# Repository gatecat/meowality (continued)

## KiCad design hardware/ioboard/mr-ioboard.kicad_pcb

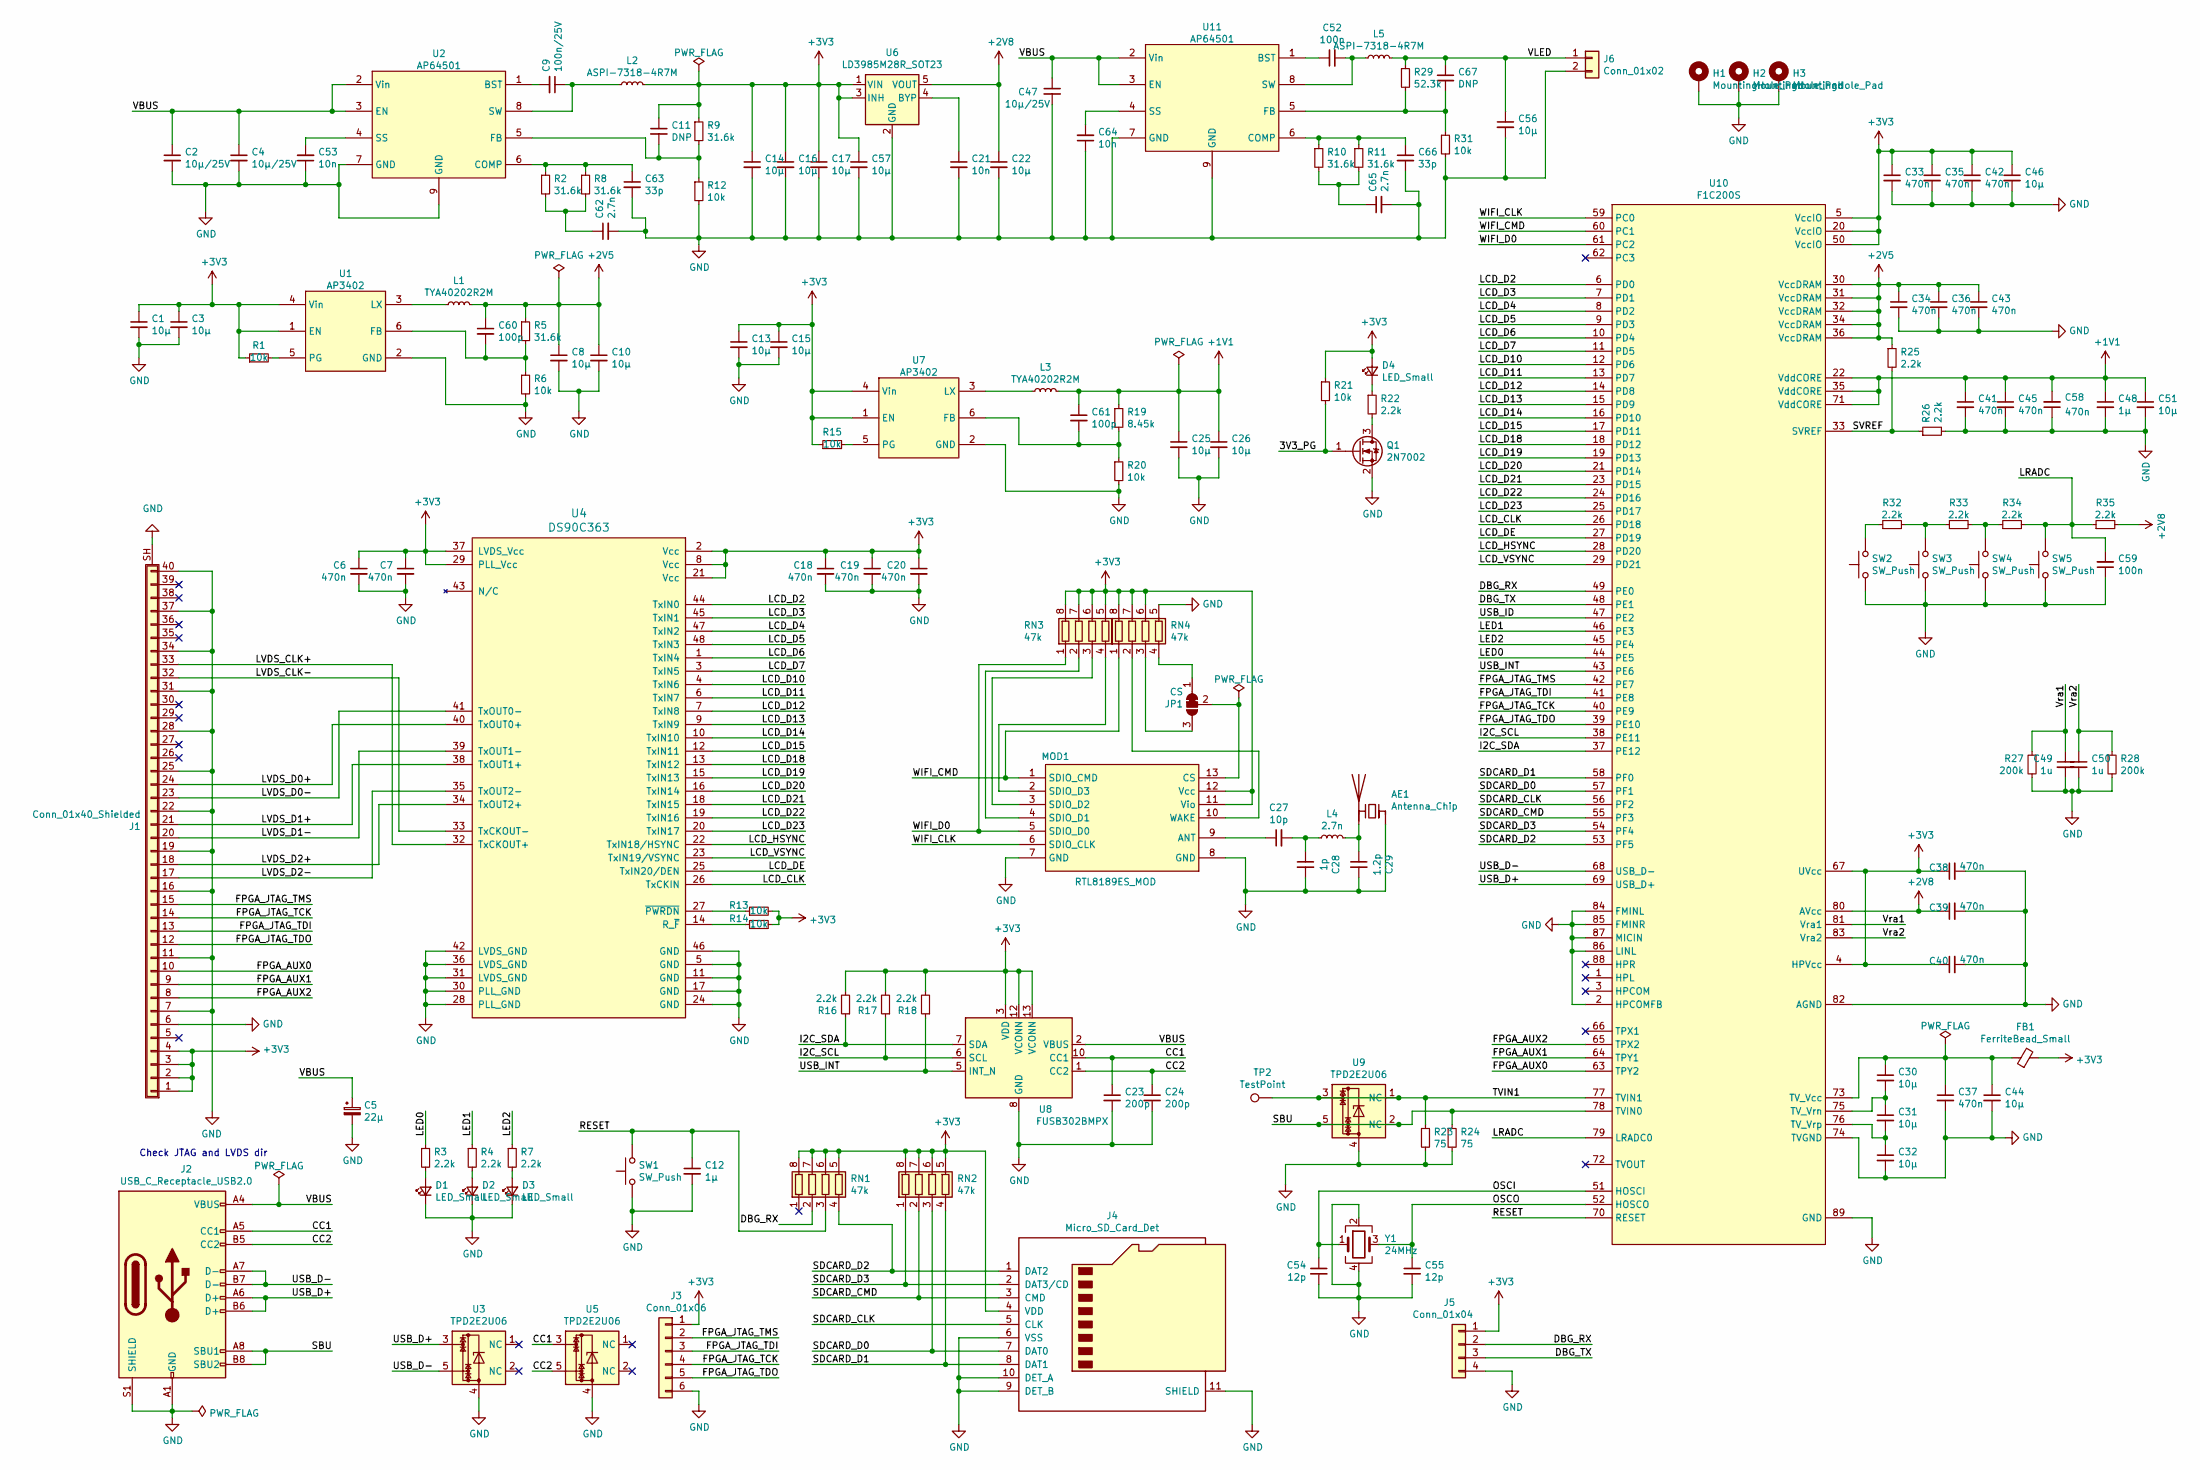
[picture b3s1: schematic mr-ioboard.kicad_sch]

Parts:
AE1: Antenna_Chip; Johanson_2450AT43F0100
C1, C3, C8, C10, C13, C14, C15, C16, C17, C22, C25, C26, C30, C31, C32, C44, C46, C51, C56, C57: 10µ; C_0805_2012Metric
C2, C4, C47: 10µ/25V; C_0805_2012Metric
C5: 22µ; CP_EIA-3528-12_Kemet-T
C6, C7, C18, C19, C20, C33, C34, C35, C36, C37, C38, C39, C40, C41, C42, C43, C45, C58: 470n; C_0402_1005Metric
C9: 100n/25V; C_0402_1005Metric
C11, C67: DNP; C_0402_1005Metric
C12, C48: 1µ; C_0603_1608Metric
C21, C53, C64: 10n; C_0402_1005Metric
C23, C24: 200p; C_0402_1005Metric
C27: 10p; C_0402_1005Metric
C28: 1p; C_0402_1005Metric
C29: 1.2p; C_0402_1005Metric
C49, C50: 1u; C_0603_1608Metric
C52, C59: 100n; C_0402_1005Metric
C54, C55: 12p; C_0402_1005Metric
C60, C61: 100p; C_0402_1005Metric
C62, C65: 2.7n; C_0402_1005Metric
C63, C66: 33p; C_0402_1005Metric
D1, D2, D3, D4: LED_Small; LED_0805_2012Metric
FB1: FerriteBead_Small; L_0603_1608Metric
H1, H2, H3: MountingHole_Pad; MountingHole_3.2mm_M3_Pad_Via
J1: Conn_01x40_Shielded; TE_FPC_40pin_p0.5mm_4-1734839-0
J2: USB_C_Receptacle_USB2.0; USB_C_Receptacle_GCT_USB4085
J3: Conn_01x06; PinHeader_1x06_P2.54mm_Vertical
J4: Micro_SD_Card_Det; microSD_HC_Hirose_DM3BT-DSF-PEJS
J5: Conn_01x04; PinHeader_1x04_P2.54mm_Vertical
J6: Conn_01x02; PinHeader_1x02_P2.54mm_Vertical
JP1: CS; SolderJumper-3_P1.3mm_Bridged12_Pad1.0x1.5mm
L1, L3: TYA40202R2M; L_Taiyo-Yuden_NR-40xx
L2, L5: ASPI-7318-4R7M; L_Bourns_SRP7028A_7.3x6.6mm
L4: 2.7n; L_0402_1005Metric
MOD1: RTL8189ES_MOD
Q1: 2N7002; SOT-23
R1, R6, R12, R13, R14, R15, R20, R21, R31: 10k; R_0402_1005Metric
R2, R5, R8, R9, R10, R11: 31.6k; R_0402_1005Metric
R3, R4, R7, R16, R17, R18, R22, R25, R26, R32, R33, R34, R35: 2.2k; R_0402_1005Metric
R19: 8.45k; R_0402_1005Metric
R23, R24: 75; R_0402_1005Metric
R27, R28: 200k; R_0402_1005Metric
R29: 52.3k; R_0402_1005Metric
RN1, RN2, RN3, RN4: 47k; R_Array_Convex_4x0402
SW1, SW2, SW3, SW4, SW5: SW_Push; SW_SPST_B3U-3000P
TP2: TestPoint; TestPoint_Pad_D2.0mm
U1, U7: AP3402; TSOT-23-6
U2, U11: AP64501; Diodes_SO-8EP
U3, U5, U9: TPD2E2U06; SOT-553
U4: DS90C363; TSSOP-48_8x12.5mm_P0.5mm
U6: LD3985M28R_SOT23; SOT-23-5
U8: FUSB302BMPX; WQFN-14-1EP_2.5x2.5mm_P0.5mm_EP1.45x1.45mm
U10: F1C200S; QFN-88_EP_10x10_Pitch0.4mm
Y1: 24MHz; Oscillator_SMD_EuroQuartz_XO32-4Pin_3.2x2.5mm

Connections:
+1V1: C25.1, C26.1, C41.1, C45.1, C48.1, C51.1, C58.2, C61.1, L3.2, R19.1, U10.22 (VddCORE), U10.35 (VddCORE), U10.71 (VddCORE)
+2V5: C8.1, C10.1, C34.1, C36.1, C43.1, C60.1, L1.2, R5.1, R25.1, U10.30 (VccDRAM), U10.31 (VccDRAM), U10.32 (VccDRAM), U10.34 (VccDRAM), U10.36 (VccDRAM)
+2V8: C22.1, C39.1, R35.2, U6.5 (VOUT), U10.80 (AVcc)
+3V3: C1.1, C3.1, C6.1, C7.1, C11.1, C13.1, C14.1, C15.1, C16.1, C17.1, C18.1, C19.1, C20.1, C33.1, C35.1, C38.1, C40.1, C42.1, C46.1, C57.1, D4.2 (A), FB1.2, J1.1, J1.2, J1.3, J1.4, J3.1, J4.4 (VDD), J5.1, L2.2, MOD1.11 (Vio), MOD1.12 (Vcc), R1.1, R9.1, R13.2, R14.2, R15.1, R16.2, R17.2, R18.2, R21.1, RN1.5 (R4.2), RN1.6 (R3.2), RN1.7 (R2.2), RN1.8 (R1.2), RN2.5 (R4.2), RN2.6 (R3.2), RN2.7 (R2.2), RN2.8 (R1.2), RN3.5 (R4.2), RN3.6 (R3.2), RN3.7 (R2.2), RN3.8 (R1.2), RN4.6 (R3.2), RN4.7 (R2.2), RN4.8 (R1.2), U1.1 (EN), U1.4 (Vin), U4.2 (Vcc), U4.8 (Vcc), U4.21 (Vcc), U4.29 (PLL_Vcc), U4.37 (LVDS_Vcc), U6.1 (VIN), U6.3 (INH), U7.1 (EN), U7.4 (Vin), U8.3 (VDD), U8.4 (VDD), U8.12 (VCONN), U8.13 (VCONN), U10.4 (HPVcc), U10.5 (VccIO), U10.20 (VccIO), U10.50 (VccIO), U10.67 (UVcc)
/3V3_PG: Q1.1 (G), R21.2
/CC1: C23.1, J2.A5 (CC1), U5.3, U8.10 (CC1), U8.11 (CC1)
/CC2: C24.1, J2.B5 (CC2), U5.5, U8.1 (CC2), U8.14 (CC2)
/DBG_RX: J5.2, RN1.2 (R2.1), U10.49 (PE0)
/DBG_TX: J5.3, U10.48 (PE1)
/FPGA_AUX0: J1.10, U10.63 (TPY2)
/FPGA_AUX1: J1.9, U10.64 (TPY1)
/FPGA_AUX2: J1.8, U10.65 (TPX2)
/FPGA_JTAG_TCK: J1.14, J3.4, U10.40 (PE9)
/FPGA_JTAG_TDI: J1.13, J3.3, U10.41 (PE8)
/FPGA_JTAG_TDO: J1.12, J3.5, U10.39 (PE10)
/FPGA_JTAG_TMS: J1.15, J3.2, U10.42 (PE7)
/I2C_SCL: R17.1, U8.6 (SCL), U10.38 (PE11)
/I2C_SDA: R16.1, U8.7 (SDA), U10.37 (PE12)
/LCD_CLK: U4.26 (TxCKIN), U10.26 (PD18)
/LCD_D2: U4.44 (TxIN0), U10.6 (PD0)
/LCD_D3: U4.45 (TxIN1), U10.7 (PD1)
/LCD_D4: U4.47 (TxIN2), U10.8 (PD2)
/LCD_D5: U4.48 (TxIN3), U10.9 (PD3)
/LCD_D6: U4.1 (TxIN4), U10.10 (PD4)
/LCD_D7: U4.3 (TxIN5), U10.11 (PD5)
/LCD_D10: U4.4 (TxIN6), U10.12 (PD6)
/LCD_D11: U4.6 (TxIN7), U10.13 (PD7)
/LCD_D12: U4.7 (TxIN8), U10.14 (PD8)
/LCD_D13: U4.9 (TxIN9), U10.15 (PD9)
/LCD_D14: U4.10 (TxIN10), U10.16 (PD10)
/LCD_D15: U4.12 (TxIN11), U10.17 (PD11)
/LCD_D18: U4.13 (TxIN12), U10.18 (PD12)
/LCD_D19: U4.15 (TxIN13), U10.19 (PD13)
/LCD_D20: U4.16 (TxIN14), U10.21 (PD14)
/LCD_D21: U4.18 (TxIN15), U10.23 (PD15)
/LCD_D22: U4.19 (TxIN16), U10.24 (PD16)
/LCD_D23: U4.20 (TxIN17), U10.25 (PD17)
/LCD_DE: U4.25 (TxIN20/DEN), U10.27 (PD19)
/LCD_HSYNC: U4.22 (TxIN18/HSYNC), U10.28 (PD20)
/LCD_VSYNC: U4.23 (TxIN19/VSYNC), U10.29 (PD21)
/LED0: R3.1, U10.44 (PE5)
/LED1: R4.1, U10.46 (PE3)
/LED2: R7.1, U10.45 (PE4)
/LRADC: C59.2, R34.2, R35.1, SW5.2, U10.79 (LRADC0)
/LVDS_CLK+: J1.33, U4.32 (TxCKOUT+)
/LVDS_CLK-: J1.32, U4.33 (TxCKOUT-)
/LVDS_D0+: J1.24, U4.40 (TxOUT0+)
/LVDS_D0-: J1.23, U4.41 (TxOUT0-)
/LVDS_D1+: J1.21, U4.38 (TxOUT1+)
/LVDS_D1-: J1.20, U4.39 (TxOUT1-)
/LVDS_D2+: J1.18, U4.34 (TxOUT2+)
/LVDS_D2-: J1.17, U4.35 (TxOUT2-)
/OSCI: C54.1, U10.51 (HOSCI), Y1.1
/OSCO: C55.1, U10.52 (HOSCO), Y1.3
/RESET: C12.1, RN1.3 (R3.1), SW1.2, U10.70 (RESET)
/SBU: J2.A8 (SBU1), J2.B8 (SBU2), R24.1, U9.2 (NC), U9.5, U10.78 (TVIN0)
/SDCARD_CLK: J4.5 (CLK), U10.56 (PF2)
/SDCARD_CMD: J4.3 (CMD), RN2.2 (R2.1), U10.55 (PF3)
/SDCARD_D0: J4.7 (DAT0), RN2.3 (R3.1), U10.57 (PF1)
/SDCARD_D1: J4.8 (DAT1), RN2.4 (R4.1), U10.58 (PF0)
/SDCARD_D2: J4.1 (DAT2), RN1.4 (R4.1), U10.53 (PF5)
/SDCARD_D3: J4.2 (DAT3/CD), RN2.1 (R1.1), U10.54 (PF4)
/SVREF: R25.2, R26.1, U10.33 (SVREF)
/TVIN1: R23.1, TP2.1, U9.1 (NC), U9.3, U10.77 (TVIN1)
/USB_D+: J2.A6 (D+), J2.B6 (D+), U3.3, U10.69 (USB_D+)
/USB_D-: J2.A7 (D-), J2.B7 (D-), U3.5, U10.68 (USB_D-)
/USB_ID: U10.47 (PE2)
/USB_INT: R18.1, U8.5 (INT_N), U10.43 (PE6)
/VBUS: C2.1, C4.1, C5.1, C47.1, J2.A4 (VBUS), J2.A9 (VBUS), J2.B4 (VBUS), J2.B9 (VBUS), U2.2 (Vin), U2.3 (EN), U8.2 (VBUS), U11.2 (Vin), U11.3 (EN)
/VLED: C56.1, C67.1, J6.1, L5.2, R29.1
/Vra1: C49.1, R27.1, U10.81 (Vra1)
/Vra2: C50.1, R28.1, U10.83 (Vra2)
/WIFI_CLK: MOD1.6 (SDIO_CLK), U10.59 (PC0)
/WIFI_CMD: MOD1.1 (SDIO_CMD), RN4.1 (R1.1), U10.60 (PC1)
/WIFI_D0: MOD1.5 (SDIO_D0), RN3.1 (R1.1), U10.61 (PC2)
GND: AE1.1 (FEED), C1.2, C2.2, C3.2, C4.2, C5.2, C6.2, C7.2, C8.2, C10.2, C12.2, C13.2, C14.2, C15.2, C16.2, C17.2, C18.2, C19.2, C20.2, C21.2, C22.2, C23.2, C24.2, C25.2, C26.2, C28.2, C29.2, C32.2, C33.2, C34.2, C35.2, C36.2, C37.2, C38.2, C39.2, C40.2, C41.2, C42.2, C43.2, C44.2, C45.2, C46.2, C47.2, C48.2, C49.2, C50.2, C51.2, C53.1, C54.2, C55.2, C56.2, C57.2, C58.1, C59.1, C62.2, C63.2, C64.1, C65.2, C66.2, D1.1 (K), D2.1 (K), D3.1 (K), H1.1, H2.1, H3.1, J1.6, J1.7, J1.11, J1.16, J1.19, J1.22, J1.25, J1.28, J1.31, J1.34, J1.37, J1.40, J1.SH (Shield), J2.A1 (GND), J2.A12 (GND), J2.B1 (GND), J2.B12 (GND), J2.S1 (SHIELD), J3.6, J4.6 (VSS), J4.9 (DET_B), J4.10 (DET_A), J4.11 (SHIELD), J5.4, J6.2, MOD1.7 (GND), MOD1.8 (GND), Q1.2 (S), R6.2, R12.2, R20.2, R23.2, R24.2, R26.2, R27.2, R28.2, R31.2, RN4.5 (R4.2), SW1.1, SW2.1, SW3.1, SW4.1, SW5.1, U1.2 (GND), U2.7 (GND), U2.9 (GND), U3.4, U4.5 (GND), U4.11 (GND), U4.17 (GND), U4.24 (GND), U4.28 (PLL_GND), U4.30 (PLL_GND), U4.31 (LVDS_GND), U4.36 (LVDS_GND), U4.42 (LVDS_GND), U4.46 (GND), U5.4, U6.2 (GND), U7.2 (GND), U8.8 (GND), U8.9 (GND), U8.15 (GND), U9.4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
unnamed: AE1.2 (PCB_Trace), C29.1, L4.2
unnamed: C9.1, L2.1, U2.8 (SW)
unnamed: C9.2, U2.1 (BST)
unnamed: C11.2, R9.2, R12.1, U2.5 (FB)
unnamed: C21.1, U6.4 (BYP)
unnamed: C27.1, MOD1.9 (ANT)
unnamed: C27.2, C28.1, L4.1
unnamed: C30.1, C37.1, C44.1, FB1.1, U10.73 (TV_Vcc)
unnamed: C30.2, C31.1, U10.75 (TV_Vrn)
unnamed: C31.2, C32.1, U10.76 (TV_Vrp)
unnamed: C52.1, U11.1 (BST)
unnamed: C52.2, L5.1, U11.8 (SW)
unnamed: C53.2, U2.4 (SS)
unnamed: C60.2, R5.2, R6.1, U1.6 (FB)
unnamed: C61.2, R19.2, R20.1, U7.6 (FB)
unnamed: C62.1, R2.2, R8.2
unnamed: C63.1, R2.1, R8.1, U2.6 (COMP)
unnamed: C64.2, U11.4 (SS)
unnamed: C65.1, R10.2, R11.2
unnamed: C66.1, R10.1, R11.1, U11.6 (COMP)
unnamed: C67.2, R29.2, R31.1, U11.5 (FB)
unnamed: D1.2 (A), R3.2
unnamed: D2.2 (A), R4.2
unnamed: D3.2 (A), R7.2
unnamed: D4.1 (K), R22.1
unnamed: JP1.1 (A), RN4.4 (R4.1)
unnamed: JP1.2 (C), MOD1.13 (CS)
unnamed: JP1.3 (B), RN4.3 (R3.1)
unnamed: L1.1, U1.3 (LX)
unnamed: L3.1, U7.3 (LX)
unnamed: MOD1.2 (SDIO_D3), RN3.4 (R4.1)
unnamed: MOD1.3 (SDIO_D2), RN3.3 (R3.1)
unnamed: MOD1.4 (SDIO_D1), RN3.2 (R2.1)
unnamed: MOD1.10 (WAKE), RN4.2 (R2.1)
unnamed: Q1.3 (D), R22.2
unnamed: R1.2, U1.5 (PG)
unnamed: R13.1, U4.27 (~PWRDN)
unnamed: R14.1, U4.14 (R_~F)
unnamed: R15.2, U7.5 (PG)
unnamed: R32.1, SW2.2
unnamed: R32.2, R33.1, SW3.2
unnamed: R33.2, R34.1, SW4.2

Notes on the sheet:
Check JTAG and LVDS dir

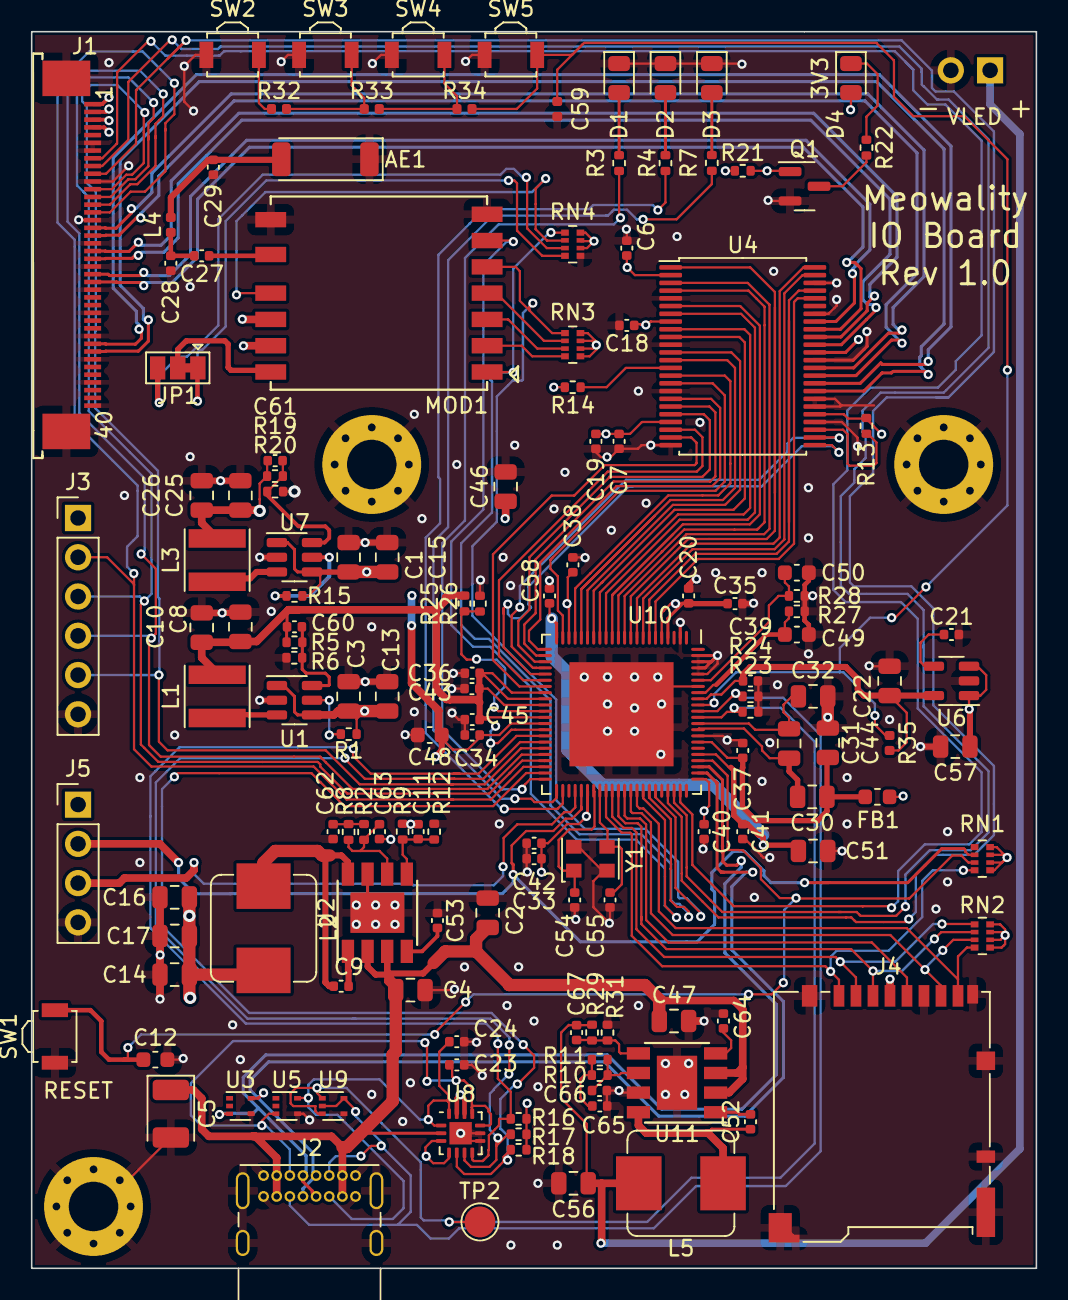
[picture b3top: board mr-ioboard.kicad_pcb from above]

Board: 4 copper layers, 65.0 x 80.0 mm, 146 parts (1 on the bottom side), 117 nets.

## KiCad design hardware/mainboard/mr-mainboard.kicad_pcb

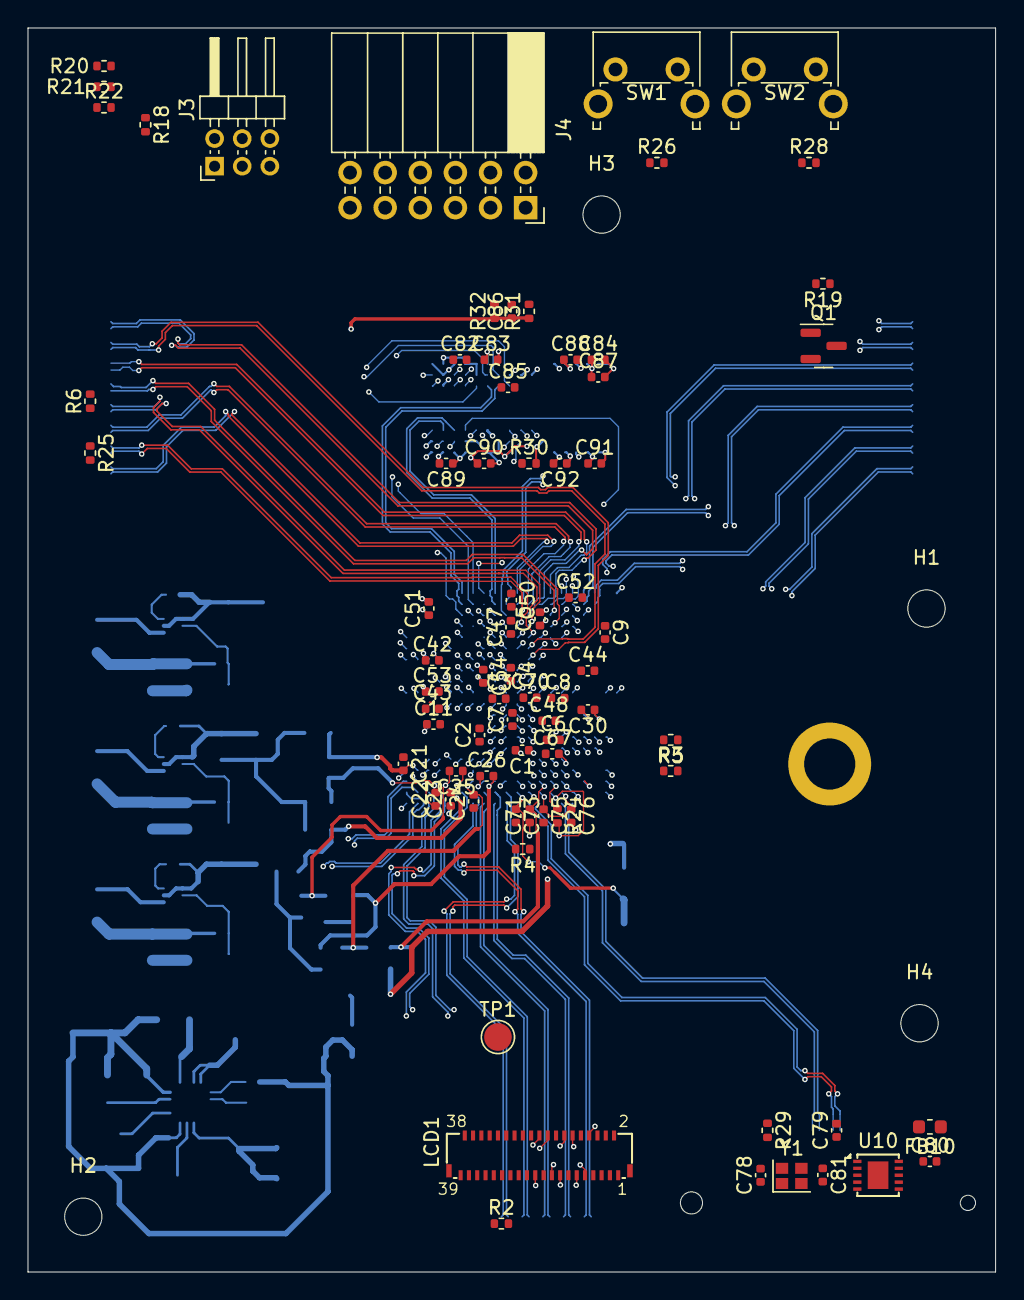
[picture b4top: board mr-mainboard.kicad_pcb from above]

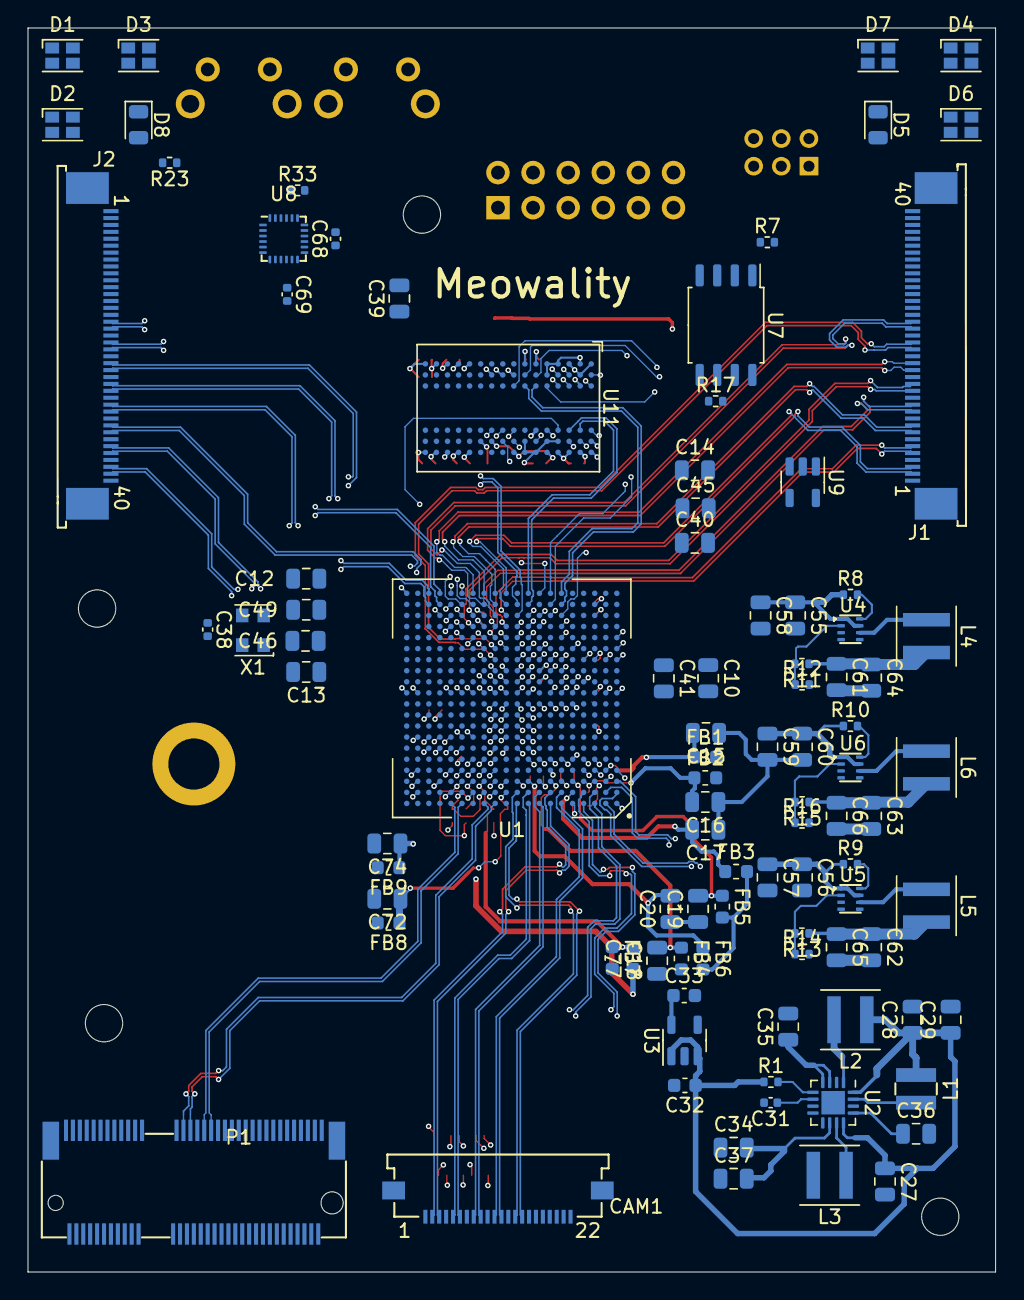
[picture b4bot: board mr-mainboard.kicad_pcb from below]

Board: 6 copper layers, 70.0 x 90.0 mm, 177 parts (96 on the bottom side), 193 nets.

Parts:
C1, C2, C3, C4, C5, C6, C7, C8, C9, C11, C38, C42, C43, C44, C47, C48, C50, C51, C52, C53, C54, C67, C68, C70, C79, C80, C82, C83, C84, C85, C86, C87, C88, C89, C90, C91, C92: 470n; C_0402_1005Metric
C10, C12, C13, C14, C15, C16, C17, C18, C19, C20, C27, C28, C29, C34, C35, C36, C37, C39, C40, C41, C45, C46, C49, C55, C56, C57, C58, C59, C60, C61, C62, C63, C64, C65, C66, C72, C74: 10µ; C_0805_2012Metric
C21, C22, C23, C24, C25, C26, C30, C31, C69, C71, C73, C75, C76: 100n; C_0402_1005Metric
C32, C33: 1µ; C_0603_1608Metric
C77: 2.2µ; C_0603_1608Metric
C78, C81: 12p; C_0402_1005Metric
CAM1: PI_CAM_22P; 54548-2271
D1, D2, D3, D4, D6, D7: LED_ABGR; LED_Cree-PLCC4_2x2mm_CW
D5, D8: LED_Small; LED_0805_2012Metric
FB1, FB2, FB3, FB4, FB5, FB6, FB7, FB8, FB9, FB10: 120; L_0603_1608Metric
H1, H2, H3, H4: MountingHole; MountingHole_2.7mm_M2.5
H5: MountingHole; 9774025151R
J1, J2: Conn_01x40_Shielded; TE_FPC_40pin_p0.5mm_4-1734839-0
J3: EAR; PinHeader_2x03_P2.00mm_Horizontal
J4: Conn_02x06_Top_Bottom; PinSocket_2x06_P2.54mm_Horizontal
L1: XFL3012-103MEB; XFL3012
L2, L3: XFL4020-472MEB; L_Coilcraft_XxL4020
L4, L5, L6: XFL4015-471MEB; L_Coilcraft_XxL4020
LCD1: H381Dxx0y.z; FH35C-39S-0.3SHW
P1: M2_SOCKET_E; 2199230-4
Q1: 2N7002; SOT-23
R1: 0; R_0402_1005Metric
R2, R8, R9, R10, R12, R14, R16, R17, R19, R25, R26, R28, R29, R33: 10k; R_0402_1005Metric
R3, R4, R5, R6, R7: 4.7k; R_0402_1005Metric
R11: 6.98k; R_0402_1005Metric
R13: 20k; R_0402_1005Metric
R15: 15k; R_0402_1005Metric
R18, R23, R31, R32: 1k; R_0402_1005Metric
R20, R21, R22: 220; R_0402_1005Metric
R24: 1.15k; R_0402_1005Metric
R30: NC; R_0402_1005Metric
SW1, SW2: SW_Push; SW_Tactile_SPST_Angled_PTS645Vx31-2LFS
TP1: TestPoint; TestPoint_Pad_D2.0mm
U1: LIFCL_40_CABGA400; BGA-400_20x20_17.0x17.0mm
U2: TPS65632R; QFN-16-1EP_3x3mm_P0.5mm_EP1.7x1.7mm
U3: TLV71330PDBV; SOT-23-5
U4, U5, U6: TPS62822; TI_VSON-HR_1.5x2mm_p0.5mm
U7: W25Q128JVS; SOIC-8_5.23x5.23mm_P1.27mm
U8: ICM-20948; InvenSense_QFN-24_3x3mm_P0.4mm
U9: 74AHC1G126; SOT-23-5
U10: Si52112-B; TDFN10_3x3mm_p0.5mm
U11: EM6GA16LBXA-12H; BGA-96_9.0x13.0mm_Layout2x3x16_P0.8mm
X1: XO32; Oscillator_SMD_EuroQuartz_XO32-4Pin_3.2x2.5mm
Y1: 25MHz; Crystal_SMD_2016-4Pin_2.0x1.6mm

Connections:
+1V0: C1.1, C2.1, C4.1, C6.1, C8.1, C10.1, C12.1, C61.1, C64.1, FB2.2, FB3.2, FB5.2, FB6.2, FB9.2, L4.2, R11.1, U1.F9 (VCC), U1.F12 (VCC), U1.J9 (VCC), U1.J12 (VCC), U1.L9 (VCC), U1.L12 (VCC), U1.N9 (VCC), U1.N11 (VCCECLK)
+1V5: C45.1, C47.1, C50.1, C63.1, C66.1, C82.1, C83.1, C84.1, C85.1, C87.1, C88.1, C89.1, C90.1, C91.1, C92.1, L6.2, R15.1, R32.2, U1.T9 (VCCIO4), U1.V8 (VCCIO4), U11.A1 (VddQ), U11.A8 (VddQ), U11.B2 (Vdd1), U11.C1 (VddQ), U11.C9 (VddQ), U11.D2 (VddQ), U11.D9 (Vdd1), U11.E9 (VddQ), U11.F1 (VddQ), U11.G7 (Vdd), U11.H2 (VddQ), U11.H9 (VddQ), U11.K2 (Vdd), U11.K8 (Vdd), U11.N1 (Vdd1), U11.N9 (Vdd1), U11.R1 (Vdd1), U11.R9 (Vdd1)
+1V8: C3.1, C5.1, C7.1, C9.1, C11.1, C13.1, C14.1, C41.1, C44.1, C46.1, C48.1, C49.1, C51.1, C52.1, C54.1, C62.1, C65.1, C68.1, C70.1, FB1.2, FB4.2, FB7.2, FB8.2, L5.2, LCD1.23 (IOVcc), LCD1.24 (IOVcc), R13.1, R33.2, U1.E5 (VCCIO7), U1.H3 (VCCIO7), U1.H9 (VCCAUX), U1.H12 (VCCAUXA), U1.K9 (VCCAUX), U1.K12 (VCCAUX), U1.N8 (VCCAUXH5), U1.N10 (VCCAUXH4), U1.N12 (VCCAUXH3), U1.N17 (VCCIO2), U1.U13 (VCCIO3), U1.U19 (VCCIO2), U1.V3 (VCCIO5), U1.V15 (VCCIO3), U8.8 (VDDIO), U8.13 (VDD)
+3V3: C27.1, C28.1, C29.1, C30.1, C32.1, C38.2, C39.1, C40.1, C42.1, C43.1, C53.1, C55.1, C56.1, C57.1, C58.1, C59.1, C60.1, C67.2, CAM1.22 (CAM_3V3), FB10.1, J1.37, J1.38, J1.39, J1.40, J2.1, J2.2, J2.3, J2.4, J3.1, J4.6, J4.12, L1.1, L2.1, P1.2 (3.3V), P1.4 (3.3V), P1.72 (3.3V), P1.74 (3.3V), R1.1, R3.2, R4.2, R5.1, R6.1, R7.2, R8.1, R9.1, R10.1, R18.1, R19.1, R23.1, R25.2, R26.2, R28.2, R29.1, U1.E15 (VCCIO0), U1.G17 (VCCIO1), U1.J18 (VCCIO1), U1.L3 (VCCIO6), U1.P3 (VCCIO6), U2.12 (PVin), U2.16 (AVin), U3.1 (IN), U3.3 (EN), U4.1 (EN), U4.7 (Vin), U5.1 (EN), U5.7 (Vin), U6.1 (EN), U6.7 (Vin), U7.8 (VCC), U9.5 (VCC), X1.4 (V+)
/Cam_Disp/CAM_CK+: CAM1.9 (CAM_CK+), U1.A8 (DPHY1_CKP/+)
/Cam_Disp/CAM_CK-: CAM1.8 (CAM_CK-), U1.B8 (DPHY1_CKN/-)
/Cam_Disp/CAM_D0+: CAM1.3 (CAM_D0+), U1.A7 (DPHY1_DP0/+)
/Cam_Disp/CAM_D0-: CAM1.2 (CAM_D0-), U1.B7 (DPHY1_DN0/-)
/Cam_Disp/CAM_D1+: CAM1.6 (CAM_D1+), U1.A9 (DPHY1_DP1/+)
/Cam_Disp/CAM_D1-: CAM1.5 (CAM_D1-), U1.B9 (DPHY1_DN1/-)
/Cam_Disp/CAM_D2+: CAM1.12 (CAM_D2+), U1.A6 (DPHY1_DP2/+)
/Cam_Disp/CAM_D2-: CAM1.11 (CAM_D2-), U1.B6 (DPHY1_DN2/-)
/Cam_Disp/CAM_D3+: CAM1.15 (CAM_D3+), U1.A10 (DPHY1_DP3/+)
/Cam_Disp/CAM_D3-: CAM1.14 (CAM_D3-), U1.B10 (DPHY1_DN3/-)
/Cam_Disp/DISP_AVDD_EN: LCD1.29 (AVdd_EN), U2.8 (AVddEN)
/Cam_Disp/DISP_AVdd: C36.1, LCD1.32 (AVdd), LCD1.33 (AVdd), U2.13 (OUTP2)
/Cam_Disp/DISP_CK+: LCD1.15 (CLK+), U1.A2 (DPHY0_CKP/+)
/Cam_Disp/DISP_CK-: LCD1.14 (CLK-), U1.B1 (DPHY0_CKN/-)
/Cam_Disp/DISP_D0+: LCD1.12 (D0+), U1.B2 (DPHY0_DP0/+)
/Cam_Disp/DISP_D0-: LCD1.11 (D0-), U1.C1 (DPHY0_DN0/-)
/Cam_Disp/DISP_D1+: LCD1.18 (D1+), U1.A3 (DPHY0_DP1/+)
/Cam_Disp/DISP_D1-: LCD1.17 (D1-), U1.B3 (DPHY0_DN1/-)
/Cam_Disp/DISP_D2+: LCD1.9 (D2+), U1.C2 (DPHY0_DP2/+)
/Cam_Disp/DISP_D2-: LCD1.8 (D2-), U1.D1 (DPHY0_DN2/-)
/Cam_Disp/DISP_D3+: LCD1.21 (D3+), U1.A4 (DPHY0_DP3/+)
/Cam_Disp/DISP_D3-: LCD1.20 (D3-), U1.B4 (DPHY0_DN3/-)
/Cam_Disp/DISP_OVdd: C35.1, LCD1.4 (OVdd), LCD1.5 (OVdd), LCD1.6 (OVdd), LCD1.34 (OVdd), LCD1.35 (OVdd), LCD1.36 (OVdd), U2.3 (OUTP1), U2.4 (FBS)
/Cam_Disp/DISP_OVss: C34.2, C37.2, LCD1.1 (OVss), LCD1.2 (OVss), LCD1.3 (OVss), LCD1.37 (OVss), LCD1.38 (OVss), LCD1.39 (OVss), U2.10 (OUTN)
/Cam_Disp/DISP_SWIRE: LCD1.28 (SWIRE), U2.9 (CTRL)
/Cam_Disp/DISP_Vci: C33.1, LCD1.25 (Vci), LCD1.26 (Vci), U3.5 (OUT)
/Connectors/SD0_REFRET: C71.1, C77.1, R24.2, U1.B14 (SD0_REFRET)
/FPGA_IO/CLK48: U1.L13 (PR17A/+/PCLKT1_2), X1.3 (OUT)
B2BL_CLKI+: J1.2, U1.W11 (PB54A/+/PCLKT3_0/VREF3_1/ADC_CP5/HS/BDQ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)
B2BL_CLKI-: J1.3, U1.Y11 (PB54B/-/PCLKC3_0/ADC_CN5/HS/BDQ60)
B2BL_CLKO+: J1.8, U1.Y12 (PB58A/+/PCLKT3_1/ADC_CP6/HS/BDQ60)
B2BL_CLKO-: J1.9, U1.W12 (PB58B/-/PCLKC3_1/ADC_CN6/HS/BDQ60)
B2BL_DI0+: J1.5, U1.V11 (PB56A/+/ADC_CP7/HS/BDQ60)
B2BL_DI0-: J1.6, U1.U11 (PB56B/-/ADC_CN7/HS/BDQ60)
B2BL_DI1+: J1.11, U1.U12 (PB62A/+/ADC_CP10/HS/BDQ60)
B2BL_DI1-: J1.12, U1.T12 (PB62B/-/ADC_CN10/HS/BDQ60)
B2BL_DI2+: J1.14, U1.V14 (PB68A/+/ADC_CP8/HS/BDQ60)
B2BL_DI2-: J1.15, U1.U14 (PB68B/-/ADC_CN8/HS/BDQ60)
B2BL_DO0+: J1.17, U1.Y13 (PB66A/+/COMP1IP/HS/BDQ60)
B2BL_DO0-: J1.18, U1.Y14 (PB66B/-/COMP1IN/HS/BDQ60)
B2BL_DO1+: J1.20, U1.R12 (PB64A/+/ADC_CP4/HS/BDQ60)
B2BL_DO1-: J1.21, U1.P12 (PB64B/-/ADC_CN4/HS/BDQ60)
B2BL_DO2+: J1.23, U1.W13 (PB60A/+/ADC_CP9/HS/BDQS60)
B2BL_DO2-: J1.24, U1.V12 (PB60B/-/ADC_CN9/HS/BDQSN60)
B2BL_MISC0: J1.31, U1.E9 (PL10B/-), U1.U1 (PB4A/+/CDR_RXP0/VREF5_1/ADC_CP0/COMP1P/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)
B2BL_MISC1: J1.32, U1.E7 (PL11A/+), U1.T1 (PB4B/-/CDR_RXN0/ADC_CN0/COMP1N/HS)
B2BL_MISC2: J1.33, U1.E8 (PL11B/-), U1.V1 (PB6A/+/PCLKT5_0/CDR_RXP1/ADC_CP1/COMP2P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)
B2BR_CLKI+: J2.33, U1.W14 (PB72A/+/PCLKT3_2/ADC_CP13/HS/BDQ76)
B2BR_CLKI-: J2.32, U1.W15 (PB72B/-/PCLKC3_2/ADC_CN13/HS/BDQ76)
B2BR_CLKO+: J2.39, U1.U15 (PB78A/+/ADC_CP11/HS/BDQ76)
B2BR_CLKO-: J2.38, U1.V16 (PB78B/-/ADC_CN11/HS/BDQ76)
B2BR_DI0+: J2.24, U1.T13 (PB74A/+/PCLKT3_3/ADC_CP14/HS/BDQ76)
B2BR_DI0-: J2.23, U1.T14 (PB74B/-/PCLKC3_3/ADC_CN14/HS/BDQ76)
B2BR_DI1+: J2.21, U1.Y15 (PB76A/+/COMP3IP/HS/BDQS76)
B2BR_DI1-: J2.20, U1.Y16 (PB76B/-/COMP3IN/HS/BDQSN76)
B2BR_DI2+: J2.18, U1.P13 (PB70A/+/COMP2IP/HS/BDQ76)
B2BR_DI2-: J2.17, U1.R13 (PB70B/-/COMP2IN/HS/BDQ76)
B2BR_DO0+: J2.36, U1.V17 (PB80A/+/ADC_CP12/HS/BDQ76)
B2BR_DO0-: J2.35, U1.U16 (PB80B/-/ADC_CN12/HS/BDQ76)
B2BR_DO1+: J2.30, U1.Y17 (PB82A/+/ADC_CP15/HS/BDQ76)
B2BR_DO1-: J2.29, U1.W17 (PB82B/-/ADC_CN15/HS/BDQ76)
B2BR_DO2+: J2.27, U1.W18 (PB84A/+/LRC_GPLL0T_IN/HS/BDQ76)
B2BR_DO2-: J2.26, U1.Y18 (PB84B/-/LRC_GPLL0C_IN/VREF3_2/HS/BDQ76)
B2BR_MISC0: J2.10, U1.E4 (PL13A/+), U1.Y2 (PB8A/+/PCLKT5_1/LLC_GPLL0T_IN/ADC_CP3/HS)
B2BR_MISC1: J2.9, U1.E3 (PL13B/-), U1.Y3 (PB8B/-/PCLKC5_1/LLC_GPLL0C_IN/ADC_CN3/HS)
B2BR_MISC2: J2.8, U1.E2 (PL15A/+), U1.R5 (PB10A/+/PCLKT5_2/ADC_CP2/COMP3P/HS)
BTN0: R26.1, SW1.2
BTN1: R28.1, SW2.2
CAM_IO0: CAM1.17 (CAM_IO0), U1.L16 (PR19A/+/PCLKT1_1)
CAM_IO1: CAM1.18 (CAM_IO1), U1.L15 (PR19B/-)
CAM_SCL: CAM1.20 (CAM_SCL), U1.L19 (PR20B/-)
CAM_SDA: CAM1.21 (CAM_SDA), U1.L20 (PR20A/+/PCLKT1_0)
DISP_~RESET: LCD1.27 (~RESET), R2.2, U1.D3 (PL8B/-)
DONE: Q1.1 (G), R19.2, U1.D12 (PT76B/-/DONE)
EAR_0: J3.2, U1.N6 (PL42A/+)
EAR_1: J3.3, U1.N7 (PL42B/-)
EAR_2: J3.4, U1.P1 (PL44A/+)
EAR_3: J3.5, U1.P2 (PL44B/-)
FLASH_CLK: R17.1, U1.E12 (PT76A/+/MCLK/PCLKT0_0), U7.6 (CLK)
FLASH_D0: U1.D13 (PT78B/-/MOSI/MD0), U7.5 (DI(IO0))
FLASH_D1: U1.D15 (PT80A/+/MISO/MD1), U7.2 (DO(IO1))
FLASH_D2: U1.D14 (PT80B/-/MD2), U7.3 (IO2)
FLASH_D3: U1.D16 (PT82A/+/MD3), U7.7 (IO3)
FLASH_~CS: R7.1, U1.E13 (PT78A/+/MCSN/PCLKT0_1), U7.1 (~CS)
GND: C1.2, C2.2, C3.2, C4.2, C5.2, C6.2, C7.2, C8.2, C9.2, C10.2, C11.2, C12.2, C13.2, C14.2, C15.1, C16.1, C17.1, C18.1, C19.1, C20.1, C21.1, C22.1, C23.1, C24.1, C25.1, C26.1, C27.2, C28.2, C29.2, C30.2, C31.2, C32.2, C33.2, C34.1, C35.2, C36.2, C37.1, C38.1, C39.2, C40.2, C41.2, C42.2, C43.2, C44.2, C45.2, C46.2, C47.2, C48.2, C49.2, C50.2, C51.2, C52.2, C53.2, C54.2, C55.2, C56.2, C57.2, C58.2, C59.2, C60.2, C61.2, C62.2, C63.2, C64.2, C65.2, C66.2, C67.1, C68.2, C69.2, C70.2, C72.2, C73.2, C74.2, C75.2, C76.2, C78.2, C79.2, C80.2, C81.2, C82.2, C83.2, C84.2, C85.2, C86.2, C87.2, C88.2, C89.2, C90.2, C91.2, C92.2, CAM1.1 (GND), CAM1.4 (GND), CAM1.7 (GND), CAM1.10 (GND), CAM1.13 (GND), CAM1.16 (GND), CAM1.19 (GND), CAM1.M, D5.1 (K), J1.1, J1.4, J1.7, J1.10, J1.13, J1.16, J1.19, J1.22, J1.25, J1.30, J1.35, J1.SH (Shield), J2.7, J2.11, J2.16, J2.19, J2.22, J2.25, J2.28, J2.31, J2.34, J2.37, J2.40, J2.SH (Shield), J3.6, J4.5, J4.11, L3.2, LCD1.7 (GND), LCD1.10 (GND)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
IMU_CLK: U1.D6 (PL6A/+), U8.23 (SCL/SCLK)
IMU_DI: U1.D8 (PL4B/-), U8.24 (SDA/SDI)
IMU_DO: U1.D7 (PL4A/+), U8.9 (SDO/AD0)
IMU_FSYNC: U1.D4 (PL8A/+), U8.11 (FSYNC)
IMU_~CS: R33.1, U1.D5 (PL6B/-), U8.22 (~CS)
JTAG_TCK: J1.27, J2.14, U1.G18 (PR13A/+/TCK/SCLK)
JTAG_TDI: J1.28, U1.F17 (PR8B/-/TDI/SSI)
JTAG_TDI_R: J2.13, U1.F19 (PR10B/-/TDO/SSO), U9.2
JTAG_TDO_L: J1.29, J2.12, U9.4
JTAG_TMS: J1.26, J2.15, R6.2, U1.F15 (PR6B/-/TMS/SCSN)
LED_1: D6.1 (A), U1.K5 (PL24A/+)
LED_2: D3.1 (A), U1.K6 (PL24B/-)
LED_3: D1.1 (A), U1.K7 (PL26A/+)
LED_4: D7.1 (A), U1.K8 (PL26B/-)
LED_5: D4.1 (A), U1.L1 (PL27A/+)
LED_6: D2.1 (A), U1.L2 (PL27B/-)
LED_B: R22.2, U1.L7 (PL32A/+/PCLKT6_1)
LED_G: R21.2, U1.L6 (PL30B/-)
LED_R: R20.2, U1.L5 (PL30A/+/PCLKT6_0)
M2_DISABLE1: P1.56 (W_DISABLE1), U1.M6 (PL38A/+)
M2_DISABLE2: P1.54 (W_DISABLE2), U1.M5 (PL36B/-)
M2_REFCLK0+: P1.47 (REFCLK0+), U10.6 (DIFF1+)
M2_REFCLK0-: P1.49 (REFCLK0-), U10.7 (DIFF1-)
M2_RX0+: P1.35 (PER0+), U1.A13 (SD0_TXDP/+)
M2_RX0-: P1.37 (PER0-), U1.A12 (SD0_TXDN/-)
M2_TX0+: P1.41 (PET0+), U1.A16 (SD0_RXDP/+)
M2_TX0-: P1.43 (PET0-), U1.A15 (SD0_RXDN/-)
M2_~RST: P1.52 (~PERST0), U1.M4 (PL36A/+)
NX_REFCLK+: U1.C12 (SD_REFCLKP), U10.8 (DIFF2+)
NX_REFCLK-: U1.C11 (SD_REFCLKN), U10.9 (DIFF2-)
unnamed: C15.2, C21.2, FB1.1, U1.D2 (VCCADPHY0)
unnamed: C16.2, C22.2, FB2.1, U1.C4 (VCCDPHY0)
unnamed: C17.2, C23.2, FB3.1, U1.B5 (VCCPLLDPHY0)
unnamed: C18.2, C24.2, FB4.1, U1.C7 (VCCADPHY1)
unnamed: C19.2, C25.2, FB5.1, U1.C5 (VCCDPHY1)
unnamed: C20.2, C26.2, FB6.1, U1.C9 (VCCPLLDPHY1)
unnamed: C31.1, U2.6 (CT)
unnamed: C69.1, U8.10 (REGOUT)
unnamed: C71.2, C77.2, FB7.1, U1.C13 (VCCPLLSD0)
unnamed: C72.1, C73.1, FB8.1, U1.B11 (VCCAUXSD)
unnamed: C74.1, C75.1, C76.1, FB9.1, U1.B13 (VCCSD0), U1.B15 (VCCSD0)
unnamed: C78.1, U10.3 (XIN), Y1.1
unnamed: C79.1, C80.1, FB10.2, U10.1 (Vdd), U10.10 (Vdd)
unnamed: C81.1, U10.2 (XOUT), Y1.3
unnamed: D1.2 (BK), D2.2 (BK), D4.2 (BK), D6.2 (BK), D7.2 (BK), R22.1
unnamed: D1.3 (GK), D2.3 (GK), D3.3 (GK), D4.3 (GK), D6.3 (GK), D7.3 (GK), R21.1
unnamed: D1.4 (RK), D2.4 (RK), D3.4 (RK), D4.4 (RK), D6.4 (RK), D7.4 (RK), R20.1
unnamed: D5.2 (A), R18.2
unnamed: D8.1 (K), Q1.3 (D)
unnamed: D8.2 (A), R23.2
unnamed: L1.2, U2.15 (SWP2)
unnamed: L2.2, U2.1 (SWP1)
unnamed: L3.1, U2.11 (SWN)
unnamed: L4.1, U4.6 (SW)
unnamed: L5.1, U5.6 (SW)
unnamed: L6.1, U6.6 (SW)
unnamed: LCD1.30 (MTP), TP1.1
unnamed: P1.55 (~PEWAKE0), R29.2
unnamed: R1.2, U2.5 (SELP2)
unnamed: R3.1, U1.D11 (PT74A/+/INITN)
unnamed: R4.1, U1.E11 (PT74B/-/PROGRAMN)
unnamed: R5.2, U1.E19 (JTAG_EN)
unnamed: R8.2, U4.8 (PG)
unnamed: R9.2, U5.8 (PG)
unnamed: R10.2, U6.8 (PG)
unnamed: R11.2, R12.1, U4.2 (FB)
unnamed: R13.2, R14.1, U5.2 (FB)
unnamed: R15.2, R16.1, U6.2 (FB)
unnamed: R24.1, U1.C14 (SD0_REXT)
unnamed: R30.2, U11.L8 (ZQ/NC)
PMOD1_1: J4.1, U1.L14 (PR17B/-)
PMOD1_2: J4.2, U1.G14 (PR15A/+)
PMOD1_3: J4.3, U1.G15 (PR15B/-)
PMOD1_4: J4.4, U1.G19 (PR13B/-)
PMOD1_7: J4.7, U1.E20 (PR11A/+/SDA/USER_SDA)
PMOD1_8: J4.8, U1.F20 (PR11B/-/SCL/USER_SCL)
PMOD1_9: J4.9, U1.F18 (PR10A/+)
PMOD1_10: J4.10, U1.F16 (PR8A/+)
PRES_R: J2.6, R25.1, U9.1
RAM_CLK+: U1.V10 (PB42B/-/HS/BDQ38), U11.J7 (CLK+)
RAM_CLK-: U1.W10 (PB44A/+/PCLKT4_0/HS/BDQ38), U11.K7 (CLK-)
RAM_DQ0: U1.U10 (PB42A/+/HS/BDQ38), U11.C8 (DB0)
RAM_DQ1: U1.V9 (PB36B/-/HS/BDQ38), U11.B8 (DB1)
RAM_DQ2: U1.R11 (PB46B/-/VREF4_2/HS/BDQ38), U11.D7 (DB2)
RAM_DQ3: U1.P9 (PB32B/-/HS/BDQ38), U11.A7 (DB3)
RAM_DQ4: U1.T10 (PB40A/+/PCLKT4_1/HS/BDQ38), U11.A3 (DB4)
RAM_DQ5: U1.R10 (PB34B/-/HS/BDQ38), U11.C3 (DB5)
RAM_DQ6: U1.T11 (PB40B/-/PCLKC4_1/HS/BDQ38), U11.A2 (DB6)
RAM_DQ7: U1.P10 (PB34A/+/HS/BDQ38), U11.C2 (DB7)
RAM_DQ8: U1.P7 (PB26A/+/HS/BDQ22), U11.F2 (DB8)
RAM_DQ9: U1.U6 (PB16B/-/HS/BDQ22), U11.G2 (DB9)
RAM_DQ10: U1.R8 (PB28A/+/HS/BDQ22), U11.E3 (DB10)
RAM_DQ11: U1.P8 (PB26B/-/HS/BDQ22), U11.H3 (DB11)
RAM_DQ12: U1.W7 (PB24A/+/PCLKT4_2/HS/BDQ22), U11.H7 (DB12)
RAM_DQ13: U1.V6 (PB20A/+/HS/BDQ22), U11.F7 (DB13)
RAM_DQ14: U1.Y7 (PB30A/+/HS/BDQ22), U11.H8 (DB14)
RAM_DQ15: U1.V7 (PB24B/-/PCLKC4_2/HS/BDQ22), U11.F8 (DB15)
RAM_DQS0+: U1.W9 (PB38A/+/HS/BDQS38), U11.C7 (DQS0+)
RAM_DQS0-: U1.Y9 (PB38B/-/HS/BDQSN38), U11.B7 (DQS0-)
RAM_DQS1+: U1.W6 (PB22A/+/HS/BDQS22), U11.F3 (DQS1+)
RAM_DQS1-: U1.Y6 (PB22B/-/HS/BDQSN22), U11.G3 (DQS1-)
RAM_STB: U1.R9 (PB32A/+/HS/BDQ38), U11.E7 (STB)
RAM_VREF: C86.1, R31.1, R32.1, U1.T6 (PB16A/+/VREF4_1/HS/BDQ22), U11.H1 (Vref)
RAM_~CS: U1.Y8 (PB30B/-/HS/BDQ22), U11.D3 (~CS)

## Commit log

2021-01-30 Initial commit; empty project
2021-01-30 Add some schematic symbols
2021-01-30 More schematic symbols
2021-01-30 Core power, disp and camera wiring
2021-01-30 FPGA IO planning
2021-01-30 Connecting up various bits
2021-01-30 Misc bits
2021-01-30 More stuff
2021-01-30 Annotate and assign some footpints
2021-01-30 Add outline README
2021-01-31 Add some footprints
2021-01-31 Add and assign more footprints
2021-01-31 First pass at placement
2021-01-31 Working on layout
2021-01-31 MIPI routing
2021-02-01 DRAM routing
2021-02-01 Interboard pair routing
2021-02-01 Power/ground routing
2021-02-02 Misc routing
2021-02-02 More misc routing
2021-02-03 First pass at routing done
2021-02-05 Misc PCB cleanup
2021-02-08 PCB tidying up
2021-02-10 Length matching as good as possible
2021-02-17 Add F1C200S symbol for IO board
2021-02-17 IO/debug board planning
2021-02-18 Working on debug/IO board
2021-02-18 Add USBC controller and ESD diodes
2021-02-19 Schematic for ear board
2021-02-19 Add WiFi module to IO board
2021-02-24 Assign some footprints & fix values for IO board
2021-02-24 Create some footprints for the IO board
2021-02-24 Initial IO board layout
2021-02-24 Add a few missing parts to IO board
2021-02-24 Update COPYING and use standard ISC
2021-02-25 Fix IO board 2.5V supply
2021-02-25 Add VLED buck regulator to IO board
2021-02-27 IO board routing
2021-03-03 First pass at routing IO board
2021-03-03 Tidy up IO board silk
2021-03-03 Some tidying up of IO board
2021-03-17 Fix side of connector on IO board
2021-03-24 mainboard: Fix some schematic ERC issues
2021-03-24 Fix ERC/DRC issues on mainboard PCB
2021-03-24 Fix IO board ERC/DRC issues
2021-03-24 Add mounting holes to IO board
2021-03-25 Mainboard mechanical tweaks
2021-03-27 Add LRADC buttons to IO board
2021-03-27 Use B3U-3000P for all buttons
2021-04-09 Use 3-pin connector for ears
2021-04-10 Add symbols for new regs due to supply issues
2021-04-10 Replace TPS62823 with AP3402 in schematics due to supply issues
2021-04-10 Replace Vbus regs with AP64501 in schematics due to supply issues
2021-04-10 Update mainboard PCB layout with new regs
2021-04-13 Update IO board PCB layout with new regs
2021-04-18 Update ear board with addressable LEDs
2021-04-19 Update some inductor part numbers
2021-04-19 Update some part numbers
2021-10-23 Add K26 pinout from PDF
2021-10-23 Add Kria K26 import script and symbol
2021-10-23 Add new main display and microdisplay symbols
2021-10-23 Fresh start with a new K26 based project
2021-10-23 Pin planning PS IO
2021-10-24 Power and MIPI pin planning
2021-10-26 Add basic power rails
2021-10-26 Add microdisplay and its power supply
2021-11-08 Add symbols for b2b edge connectors
2021-11-08 Pin planning the main b2b connectors
2021-11-11 Initial pin plan for front b2b connector
2021-11-11 Begin front board schematic
2021-11-12 SD card, ULPI PHY, JTAG/UART
2021-11-18 Add PCIe and camera to front board
2021-11-20 Add some general control IO
2021-11-20 Add skeleton of left IO board
2021-11-20 Add USB hub and UART ICs
2021-11-20 Add Displayport connector
2021-11-20 Add Vbus to 5V buck
2021-11-21 Add type-C mux; IO exp; 3.3V/1.8V rails
2021-11-21 Add IMU
2021-11-21 Connecting some misc SoM IO
2021-11-22 Fixing various top board issues
2021-11-22 Fixing various IO board issues
2021-11-23 Fixing various front and top board issues
2021-11-23 Fix MPSoC pinout issues
2021-11-24 Working on Kria connector footprint generation
2021-11-27 Add FF0881SA1 footprint
2021-11-27 Add MET008431401101 footprint
2021-11-27 Add 245863060104829 footprint
2021-11-28 Add 84P and 140P card edge footprints
2021-11-28 Add MLP44-24L footprint
2021-11-28 Add ME1014010101011 footprint
2021-11-28 Assign most top-board footprints
2021-11-29 Replace type-C power with good ol' barrel jack
2022-01-12 Respin, v2
2022-01-12 Design updates
2022-01-12 Re-add USB-C PD control
2022-01-13 ERC fixes
2022-01-13 Add some footprint mappings
2022-01-14 Add footprint for Harting debug connector
2022-01-14 Footprint assignments and related fixes
2022-01-14 Add mini Displayport connector footprint
2022-01-14 Rework power arch to add 3V3PL; 5x PL RGB LEDs
2022-01-14 Footprint assignment updates
2022-01-14 Outline floorplan and design rule setup
2022-01-14 Update README with new project direction
2022-01-15 Add separate reg for 3V3PL
2022-01-15 Initial 'floorplan' outline
2022-01-15 Placement snapshot
2022-01-15 Placement snapshot 2
2022-01-15 Placement snapshot 3
2022-01-15 All parts placed
2022-01-15 Tidy up silk
2022-01-16 Add TVS on 5V and Vbus
2022-01-23 Mechanical updates; add cam clk connectors
2022-01-30 Fix LCD connector rotation
2022-01-30 Minor layout changes
2022-01-30 Alternate DP connector
2022-02-02 Begin some routing
2022-02-02 First pass high-speed routing
2022-02-12 High speed bits routed
2022-02-12 Misc signal breakout/routing
2022-02-13 Finish SD/ULPI routes
2022-02-13 Initial power routing
2022-02-13 Route and pinswap PL LEDs
2022-02-16 Tidy up power routes
2022-02-18 Debug signal pinswaps and routing
2022-02-20 USB and other misc routing
2022-02-20 Routing various remaining bits
2022-02-21 Routing misc stuff
2022-02-21 Add ground plane
2022-03-02 Add forgotten M.2 mounting hole
2022-03-02 Add a keepout area for the SOM standoffs
2022-03-04 Some length tuning
2022-03-05 More length/skew tuning
2022-03-05 Diff pairs all tuned
2022-03-06 Fixup Kria footprint
2022-03-29 Adding some 3D model config
2022-03-29 Rework LCD PWM setup
2022-05-01 Fix some ERC/DRC issues
2023-08-14 kicad update
2023-08-14 3d models etc
2023-08-15 Misc tweaks
2023-08-16 hardware: LED associated DFM improvement
2023-08-16 hardware: Tidying up routing
